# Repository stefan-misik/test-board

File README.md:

# test-board
Simple development board with interface to Nokia 5110 display and matrix keypad and two outputs based on Atmega328 microcontroller

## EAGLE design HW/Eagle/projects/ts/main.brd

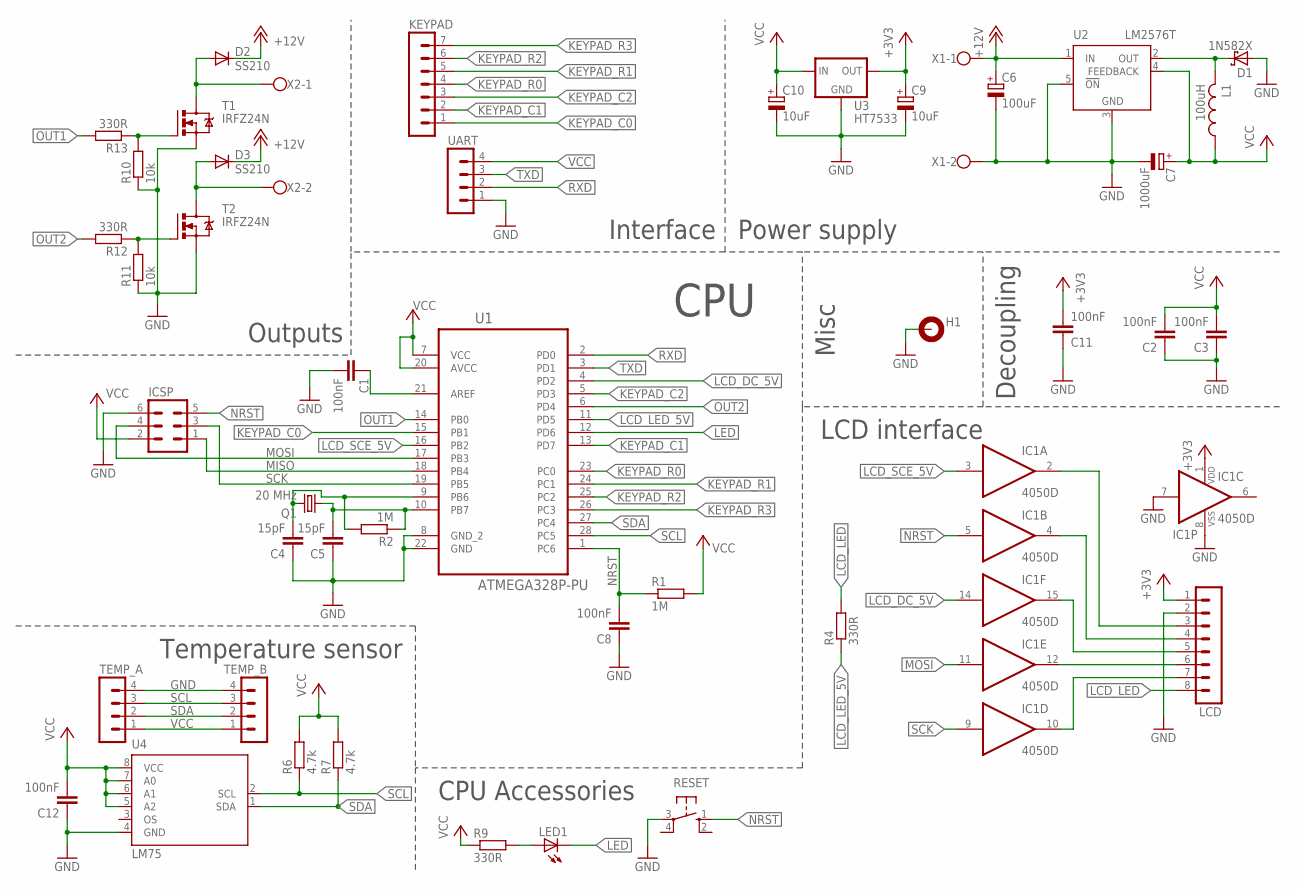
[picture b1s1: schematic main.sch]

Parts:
C1, C2, C3, C8, C11, C12: 100nF; C0805
C4, C5: 15pF; C0805
C6: 100uF; TAP5-80
C7: 1000uF; TT5D10
C9, C10: 10uF; PANASONIC_C
D1: 1N582X; DIODE5MM
D2, D3: SS210; SMB
H1: MOUNT-PAD-ROUND3.6; 3,6-PAD
IC1: 4050D; SO16
ICSP: MA03-2
KEYPAD: MA07-1
L1: 100uH; TJ3-U1
LCD: MA08-1
LED1: LED5MM
Q1: 20 MHz; HC49/S
R1, R2: 1M; R0805
R4, R9, R12, R13: 330R; R0805
R6, R7: 4.7k; R0805
R10, R11: 10k; R0805
RESET: 10-XX; B3F-10XX
T1, T2: IRFZ24N; TO220AB
TEMP_A: MA04-1
TEMP_B: MA04-1
U1: ATMEGA328P-PU; DIP254P762X457-28
U2: LM2576T; TO220-5
U3: HT7533; TO-92
U4: LM75; SOIC8
UART: MA04-1
X1, X2: W237-102

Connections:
+3V3: C9.+, C11.2, IC1.1 (VDD), LCD.1, U3.3 (OUT)
+12V: C6.+, D2.C, D3.C, U2.1 (IN), X1.1
GND: C1.2, C2.1, C3.1, C4.1, C5.1, C6.-, C7.-, C8.1, C9.-, C10.-, C11.1, C12.1, D1.A, H1.B3,6, IC1.7 (I), IC1.8 (VSS), ICSP.6, LCD.2, R10.1, R11.1, RESET.3, T1.S, T2.S, TEMP_A.4, TEMP_B.4, U1.8 (GND_2), U1.22 (GND), U2.3 (GND), U2.5 (!ON), U3.1 (GND), U4.4 (GND), UART.1, X1.2
KEYPAD_C0: KEYPAD.1, U1.15 (PB1)
KEYPAD_C1: KEYPAD.2, U1.13 (PD7)
KEYPAD_C2: KEYPAD.3, U1.5 (PD3)
KEYPAD_R0: KEYPAD.4, U1.23 (PC0)
KEYPAD_R1: KEYPAD.5, U1.24 (PC1)
KEYPAD_R2: KEYPAD.6, U1.25 (PC2)
KEYPAD_R3: KEYPAD.7, U1.26 (PC3)
LCD_DC: IC1.15 (O), LCD.5
LCD_DC_5V: IC1.14 (I), U1.4 (PD2)
LCD_LED: LCD.8, R4.2
LCD_LED_5V: R4.1, U1.11 (PD5)
LCD_MOSI: IC1.12 (O), LCD.6
LCD_RST: IC1.4 (O), LCD.4
LCD_SCE: IC1.2 (O), LCD.3
LCD_SCE_5V: IC1.3 (I), U1.16 (PB2)
LCD_SCK: IC1.10 (O), LCD.7
LED: LED1.K (C), U1.12 (PD6)
MISO: ICSP.1, U1.18 (PB4)
MOSI: IC1.11 (I), ICSP.4, U1.17 (PB3)
unnamed: C1.1, U1.21 (AREF)
unnamed: C5.2, Q1.1, R2.1, U1.10 (PB7)
unnamed: C4.2, Q1.2, R2.2, U1.9 (PB6)
unnamed: LED1.A, R9.2
unnamed: R10.2, R13.1, T1.G
unnamed: R11.2, R12.1, T2.G
NRST: C8.2, IC1.5 (I), ICSP.5, R1.1, RESET.1 (S), U1.1 (PC6)
OUT1: R13.2, U1.14 (PB0)
OUT1_OC: D2.A, T1.D, X2.1
OUT2: R12.2, U1.6 (PD4)
OUT2_OC: D3.A, T2.D, X2.2
OUT_5V: D1.C, L1.2, U2.2 (OUT)
RXD: U1.2 (PD0), UART.2
SCK: IC1.9 (I), ICSP.3, U1.19 (PB5)
SCL: R6.1, TEMP_A.3, TEMP_B.3, U1.28 (PC5), U4.2 (SCL)
SDA: R7.1, TEMP_A.2, TEMP_B.2, U1.27 (PC4), U4.1 (SDA)
TXD: U1.3 (PD1), UART.3
VCC: C2.2, C3.2, C7.+, C10.+, C12.2, ICSP.2, L1.1, R1.2, R6.2, R7.2, R9.1, TEMP_A.1, TEMP_B.1, U1.7 (VCC), U1.20 (AVCC), U2.4 (FEEDBACK), U3.2 (IN), U4.5 (A2), U4.6 (A1), U4.7 (A0), U4.8 (VCC), UART.4

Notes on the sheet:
Outputs
Temperature sensor
LCD interface
Power supply
Interface
CPU Accessories
Decoupling
Misc
CPU

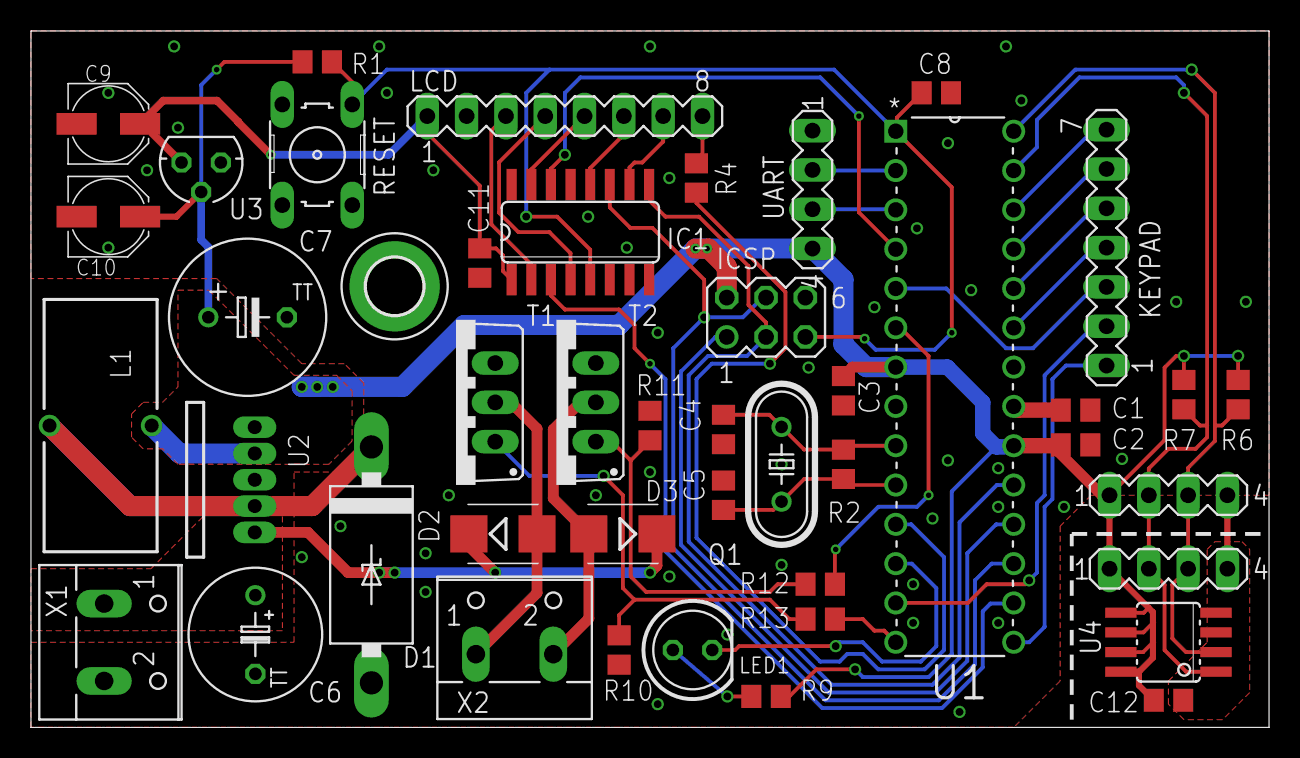
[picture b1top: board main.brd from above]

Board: 2 copper layers, 80.0 x 45.0 mm, 45 parts (0 on the bottom side), 40 nets.

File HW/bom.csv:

Qty;Value;Device;Package;Parts;Description;gme.cz;Price (CZK)
1;;10-XX;B3F-10XX;RESET;OMRON SWITCH;630-305;3,3
1;;DIODE-MINIMELF;MINIMELF;D4;DIODE;917-054;0,88
1;;LED5MM;LED5MM;LED1;LED;"511-226; 511-227";2,2
1;;MA03-1;MA03-1;UART;PIN HEADER;832-021;11
1;;MA03-2;MA03-2;ICSP;PIN HEADER;832-035;9,6
1;;MA07-1;MA07-1;KEYPAD;PIN HEADER;832-021;
1;;MA08-1;MA08-1;LCD;PIN HEADER;832-021;
2;;W237-102;W237-102;X1, X2;WAGO SCREW CLAMP;821-134;3,2
2;0R;R-EU_R0805;R0805;R3, R5;RESISTOR, European symbol;901-170;1,1
1;1000uF;CPOL-EUTT5D10;TT5D10;C7;POLARIZED CAPACITOR, European symbol;123-776;4,4
6;100nF;C-EUC0805;C0805;C1, C2, C3, C8, C11, C12;CAPACITOR, European symbol;906-096;0,75
1;100uF;CPOL-EUTAP5-80;TAP5-80;C6;POLARIZED CAPACITOR, European symbol;123-451;0,61
1;100uH;L-USTJ3-U1;TJ3-U1;L1;INDUCTOR, American symbol;611-140;19
3;10k;R-EU_R0805;R0805;R1, R10, R11;RESISTOR, European symbol;901-003;0,85
2;10uF;CPOL-EUC;PANASONIC_C;C9, C10;POLARIZED CAPACITOR, European symbol;908-003;2,6
2;15pF;C-EUC0805;C0805;C4, C5;CAPACITOR, European symbol;906-078;0,96
1;1M;R-EU_R0805;R0805;R2;RESISTOR, European symbol;901-182;1,2
1;1N582X;1N582X;DIODE5MM;D1;;223-004;3,1
1;20 MHz;CRYSTALHC49S;HC49/S;Q1;CRYSTAL;131-027;11
4;330R;R-EU_R0805;R0805;R4, R9, R12, R13;RESISTOR, European symbol;901-083;0,85
3;4.7k;R-EU_R0805;R0805;R6, R7, R8;RESISTOR, European symbol;901-115;0,85
1;4050D;4050D;SO16;IC1;Hex non-inverting BUFFER;953-067;6,6
1;ATMEGA328P-PU;ATMEGA328P-PU;DIP254P762X457-28;U1;8-bit Microcontroller with In-System Programmable Flash;432-228;94
1;HT7533;LE33CZ;TO-92;U3;;330-117;24
2;IRFZ24N;IRFZ24N;TO220AB;T1, T2;;213-208;12
1;LM2576T;LM2576T;TO220-5;U2;;330-113;40
1;LM75;LM75;SOIC8;U4;;969-012;18
1;MOUNT-PAD-ROUND3.6;MOUNT-PAD-ROUND3.6;3,6-PAD;H1;MOUNTING PAD, round;;
2;SS210;DIODE-SMB;SMB;D2, D3;DIODE;920-123;2,6

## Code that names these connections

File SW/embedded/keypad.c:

#include "keypad.h"
#include "common.h"
#include <avr/pgmspace.h>


#define keypad_get_rows() (PINC & 0x0f)

/**
 * @brief Keypad layout
 * 
 */
static const unsigned char keypad_layout[4][3] PROGMEM =
{
    {'1', '2', '3'},
    {'4', '5', '6'},
    {'7', '8', '9'},
    {'*', '0', '#'}
};


static char keypad_get_column(
    char column 
)
{
    unsigned char rows = keypad_get_rows();
    char pos;
    
    for(pos = 0; pos < 4; pos ++)
    {
        if(0 == (0x08 & rows))
            return pgm_read_byte(&(keypad_layout[pos][column]));
        
        rows <<= 1;
    }

    return '\0';
}

/******************************************************************************/
void keypad_init(
    void
)
{
    /* port connection: columns: PB1, PB2, PD7 and rows: PC0 - PC3 */
    
    /* Make sure internal pull-ups are not disabled */
    MCUCR &= ~(1 << PUD);
    
    /* Set all keypad pins as inputs to enable pull-ups */
    DDRB &= ~((1 << DDB1));
    DDRD &= ~((1 << DDD3) | (1 << DDD7));
    DDRC &= ~((1 << DDC0) | (1 << DDC1) | (1 << DDC2) | (1 << DDC3));
    
    /* Turn on the internal pull-ups */
    PORTB |= ((1 << PORTB1));
    PORTD |= ((1 << PORTD3) | (1 << PORTD7));
    PORTC |= ((1 << PORTC0) | (1 << PORTC1) | (1 << PORTC2) | (1 << PORTC3));
}

/******************************************************************************/
char keypad_get(
    void
)
{
    char key = '\0';

    /* Select first column */
    PORTD &= ~(1 << PORTD3);
    DDRD |= (1 << DDD3);
    /* Read key */
    key = keypad_get_column(0);
    /* De-select first column */
    DDRD &= ~(1 << DDD3);
    PORTD |= (1 << PORTD3);

	if ('\0' != key)
	{
		return key;
	}
    
    /* Select second column */
    PORTB &= ~(1 << PORTB1);
    DDRB |= (1 << DDB1);
    /* Read key */
    key = keypad_get_column(2);
    /* De-select second column */
    DDRB &= ~(1 << DDB1);
    PORTB |= (1 << PORTB1);

	if ('\0' != key)
	{
		return key;
	}
    
    /* Select first column */
    PORTD &= ~(1 << PORTD7);
    DDRD |= (1 << DDD7);
    /* Read key */
    key = keypad_get_column(1);
    /* De-select first column */
    DDRD &= ~(1 << DDD7);
    PORTD |= (1 << PORTD7);
    
    return key;
}

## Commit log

2015-01-07 Created directory structure
2015-01-07 Eagle description files, Design rules for iteadstudio
2015-01-07 Designed power supply
2015-01-07 Deleted files
2015-01-07 Ignored files
2015-01-08 3.3v supply
2015-01-08 v-regulators library
2015-01-08 Added level shifter CMOS 4050
2015-01-08 Added Eagle Libraries
2015-01-08 Many changes
2015-01-08 Moved power pins of 4050
2015-01-08 Resized analog ground
2015-01-08 Commit before changing to digital temperature sensor
2015-01-09 Big Update
2015-01-09 Swaped LCD_SCE_5V and LCD_DC_5V signals on 4050
2015-01-09 Added Power CMOS transistors
2015-01-10 HW Release 1
2015-01-10 Minor HW changes
2015-01-10 Timer 1 is no longer used for PWM
2015-01-10 Minor HW Updates
2015-01-10 Preparing Gerber files
2015-01-10 Generated final version of gerber files
2015-01-12 Added graphTest tool
2015-01-12 Removed unnecessary file
2015-01-13 Ignored some files
2015-01-15 Added filters into visual studio project
2015-01-19 Ignored Eagle backup files
2015-01-19 Added value of crystal
2015-01-19 Created BOM file
2015-01-19 Added order numbers in bom.csv
2015-01-22 Ignored pdb files
2015-01-22 Modified drawing technique
2015-01-22 Added Graphical library
2015-01-26 Added PCB images
2015-01-26 Modified PCB images
2015-02-01 Changed diameters of vias
2015-02-01 Changed faulty size of via
2015-03-31 Added lcd driver files
2015-03-31 minor update
2015-03-31 Added SPI communication
2015-04-01 Added module for controling outputs
2015-04-01 Working initialization, lcd parameters configuration and simple drawing
2015-04-02 Added text drawing functionality
2015-04-02 Added comments
2015-04-02 Added Main fiele, makefile and atmel studio solution to embedded part of the software
2015-04-02 Added temperature sensor driver
2015-04-02 Simple temperature meter
2015-04-03 LCD backlight and LED controlled by PWM
2015-04-03 Added function to read graphic data from display buffer
2015-04-03 Replaced inefective modulus operations
2015-04-03 Temperature resolution changed to quarter of dg
2015-04-08 Added timer module
2015-04-10 Replaced R1 due to improper LCD reset procedure
2015-04-12 Added size statistics after build
2015-04-12 Lcd content update by providing rectangle to update
2015-04-17 Temperature is read using interrupts
2015-04-18 Temperature measurement made more fail-proof
2015-04-18 Added new-lines at the end of c files
2015-04-20 Removed unnecessary typedef
2015-04-20 Comments added
2015-04-20 Added function to check status of temperature measurement
2015-04-21 Tabs replaced with spaces
2015-04-21 Added some alarm functionality to timer module
2015-04-22 Alarm functionality moved into separate module
2017-12-09 [SW] Minor changes in LCD, added keypad
    Added correct stdio putchar function for LCD. Added keypad source files.
2017-12-12 [HW] Updated PCB
    Fixed keypad connection. Removed copper from underneath the temperature
    sensor. Made temperature sensor removable.
2017-12-13 [SW] Fixed LCD redraw
2017-12-13 [HW] LCD chip select
    Using NSS microcontroller output to drive LCD chip select.
2017-12-15 [SW] Minor changes, added more LCD characters
2017-12-15 [SW] Fixed SPI clock speed for LCD
2017-12-15 [SW] Updated keypad driver
2017-12-20 [HW] Minor modifications
2017-12-21 [HW] Removed some parts, updated layout
    Removed unessential parts (0 Ohm resistor, reset pin protection diode).
    Optimized layout to optimize some connections.
2018-01-02 [HW] Minor change
2018-04-14 [HW] Organized schematics
2018-11-20 [HW] Resolved some design DRC and ERC warnings
2018-11-25 [HW] Removed old gerber files
2018-12-15 [HW] Added KiCad project with schematics
2018-12-16 [HW] Fixed issues in the KiCad schematics
    Fixed some footprints associations, 4050 buffer power supply.
2018-12-17 [SW] Modifications for the 2nd revision of the HW
2018-12-18 [SW] Basic keypad driver
2019-02-04 [SW] Added FIFO tests
2019-02-04 [SW] Ignored VS code project settings
2019-02-05 [SW] Added FIFO tests and functionality
2020-11-11 [SW] Add fuses programming
2020-12-18 [HW] Place KiCad layout components
2020-12-20 [HW] Add some layout
